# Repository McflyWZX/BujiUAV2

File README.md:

# BujiCore(AllwinnerH5CoreBoard)
 基于全志H5的M.2接口核心板，搭载4*DDR3、eMMC。
 板子使用KiCAD设计
 designed with KiCAD

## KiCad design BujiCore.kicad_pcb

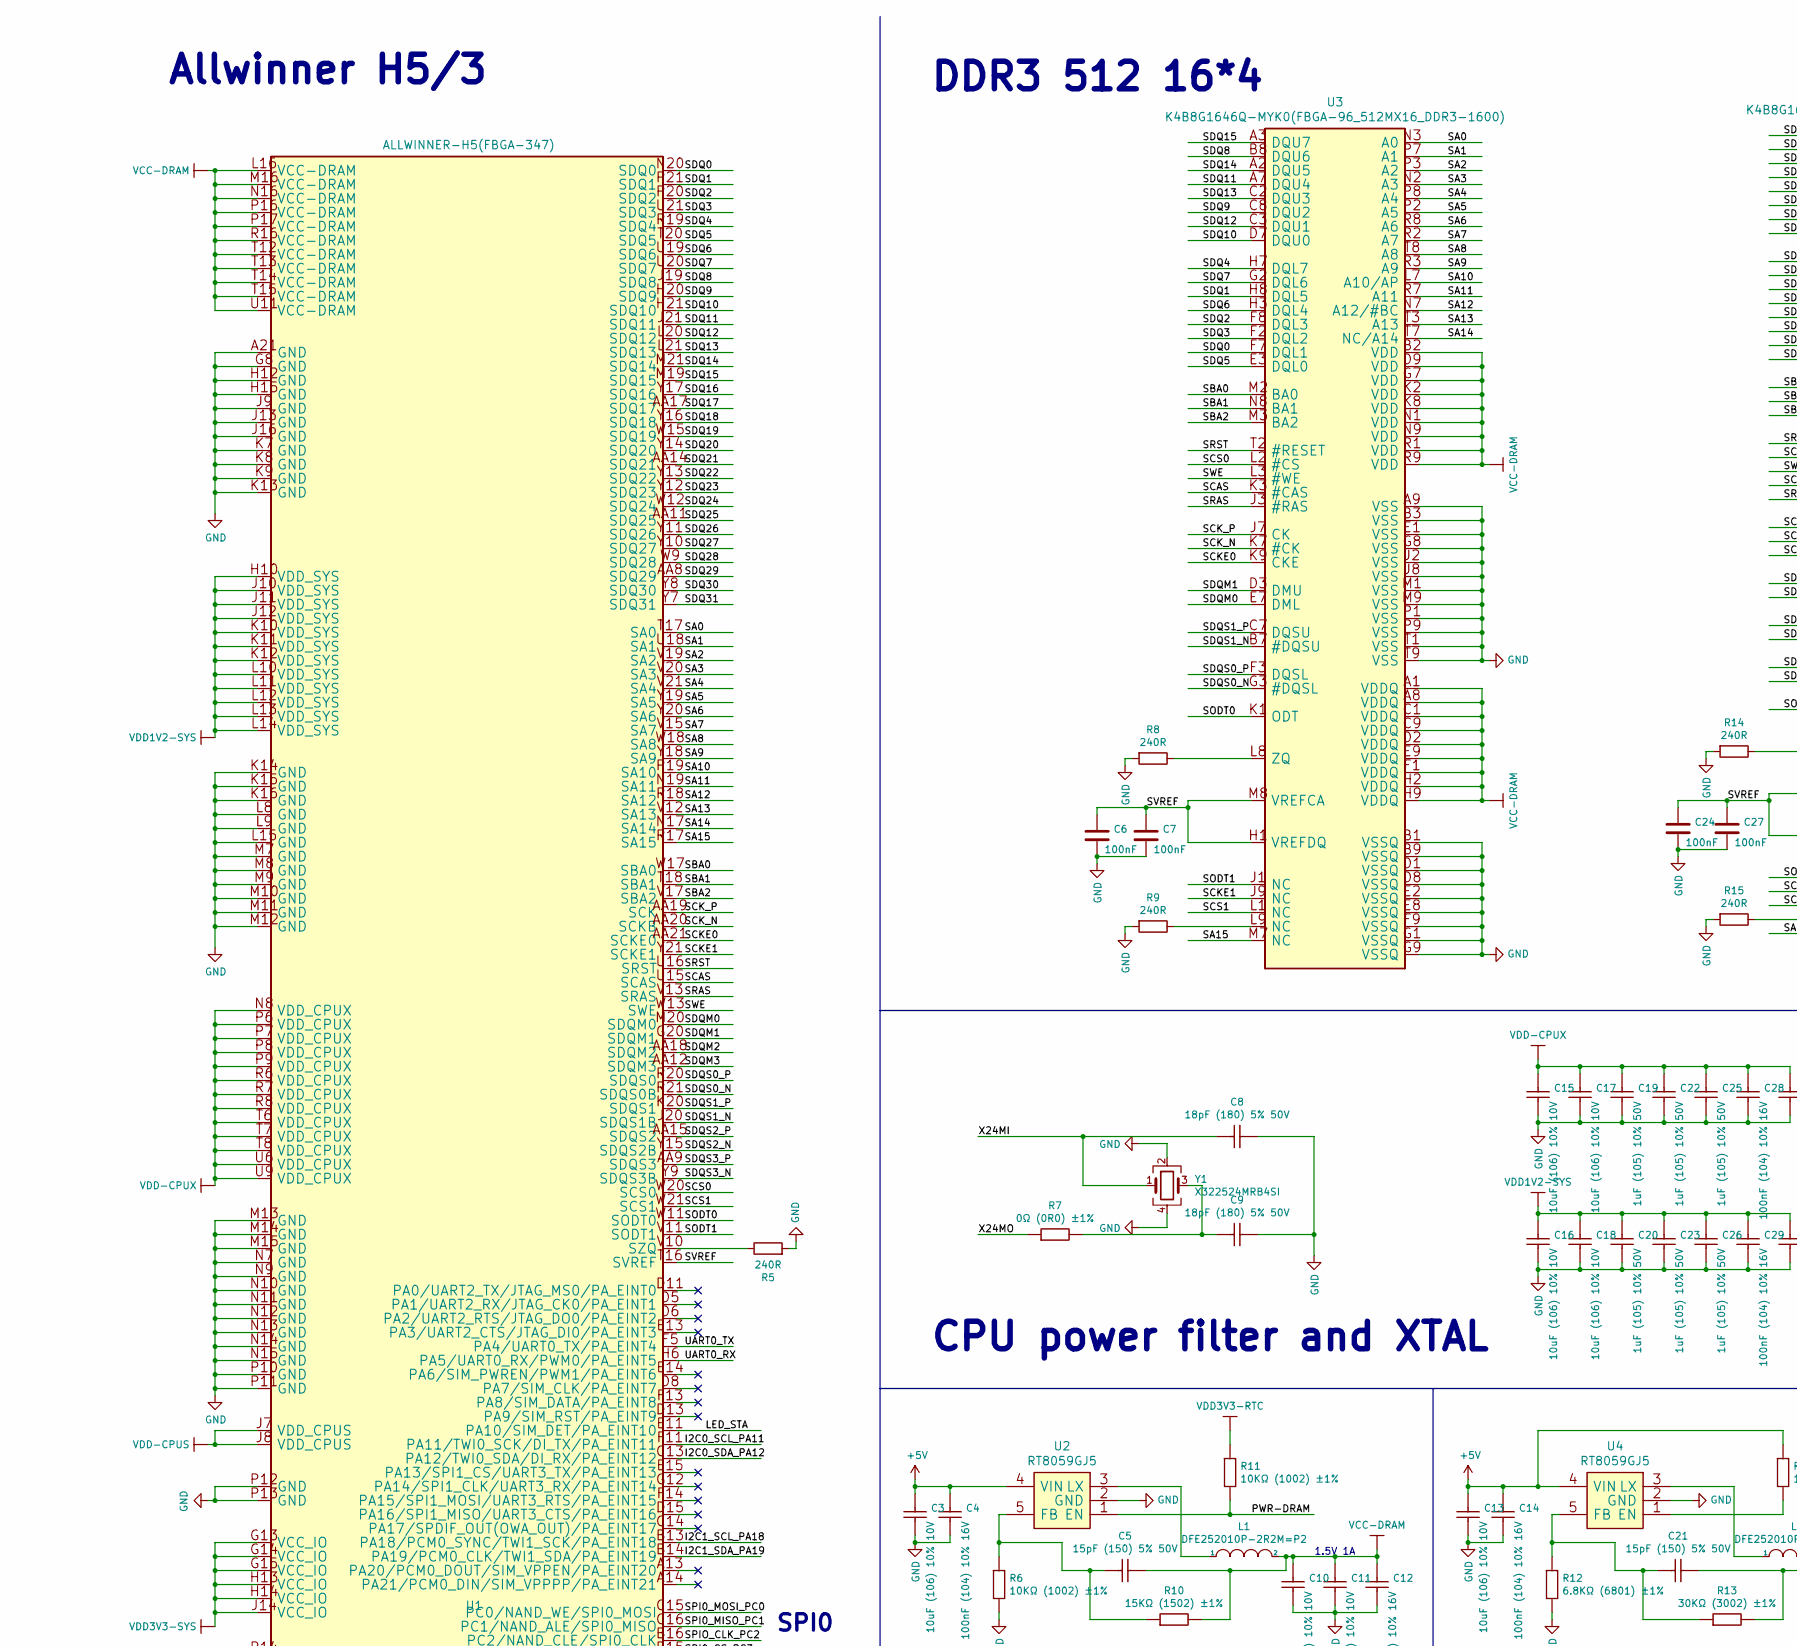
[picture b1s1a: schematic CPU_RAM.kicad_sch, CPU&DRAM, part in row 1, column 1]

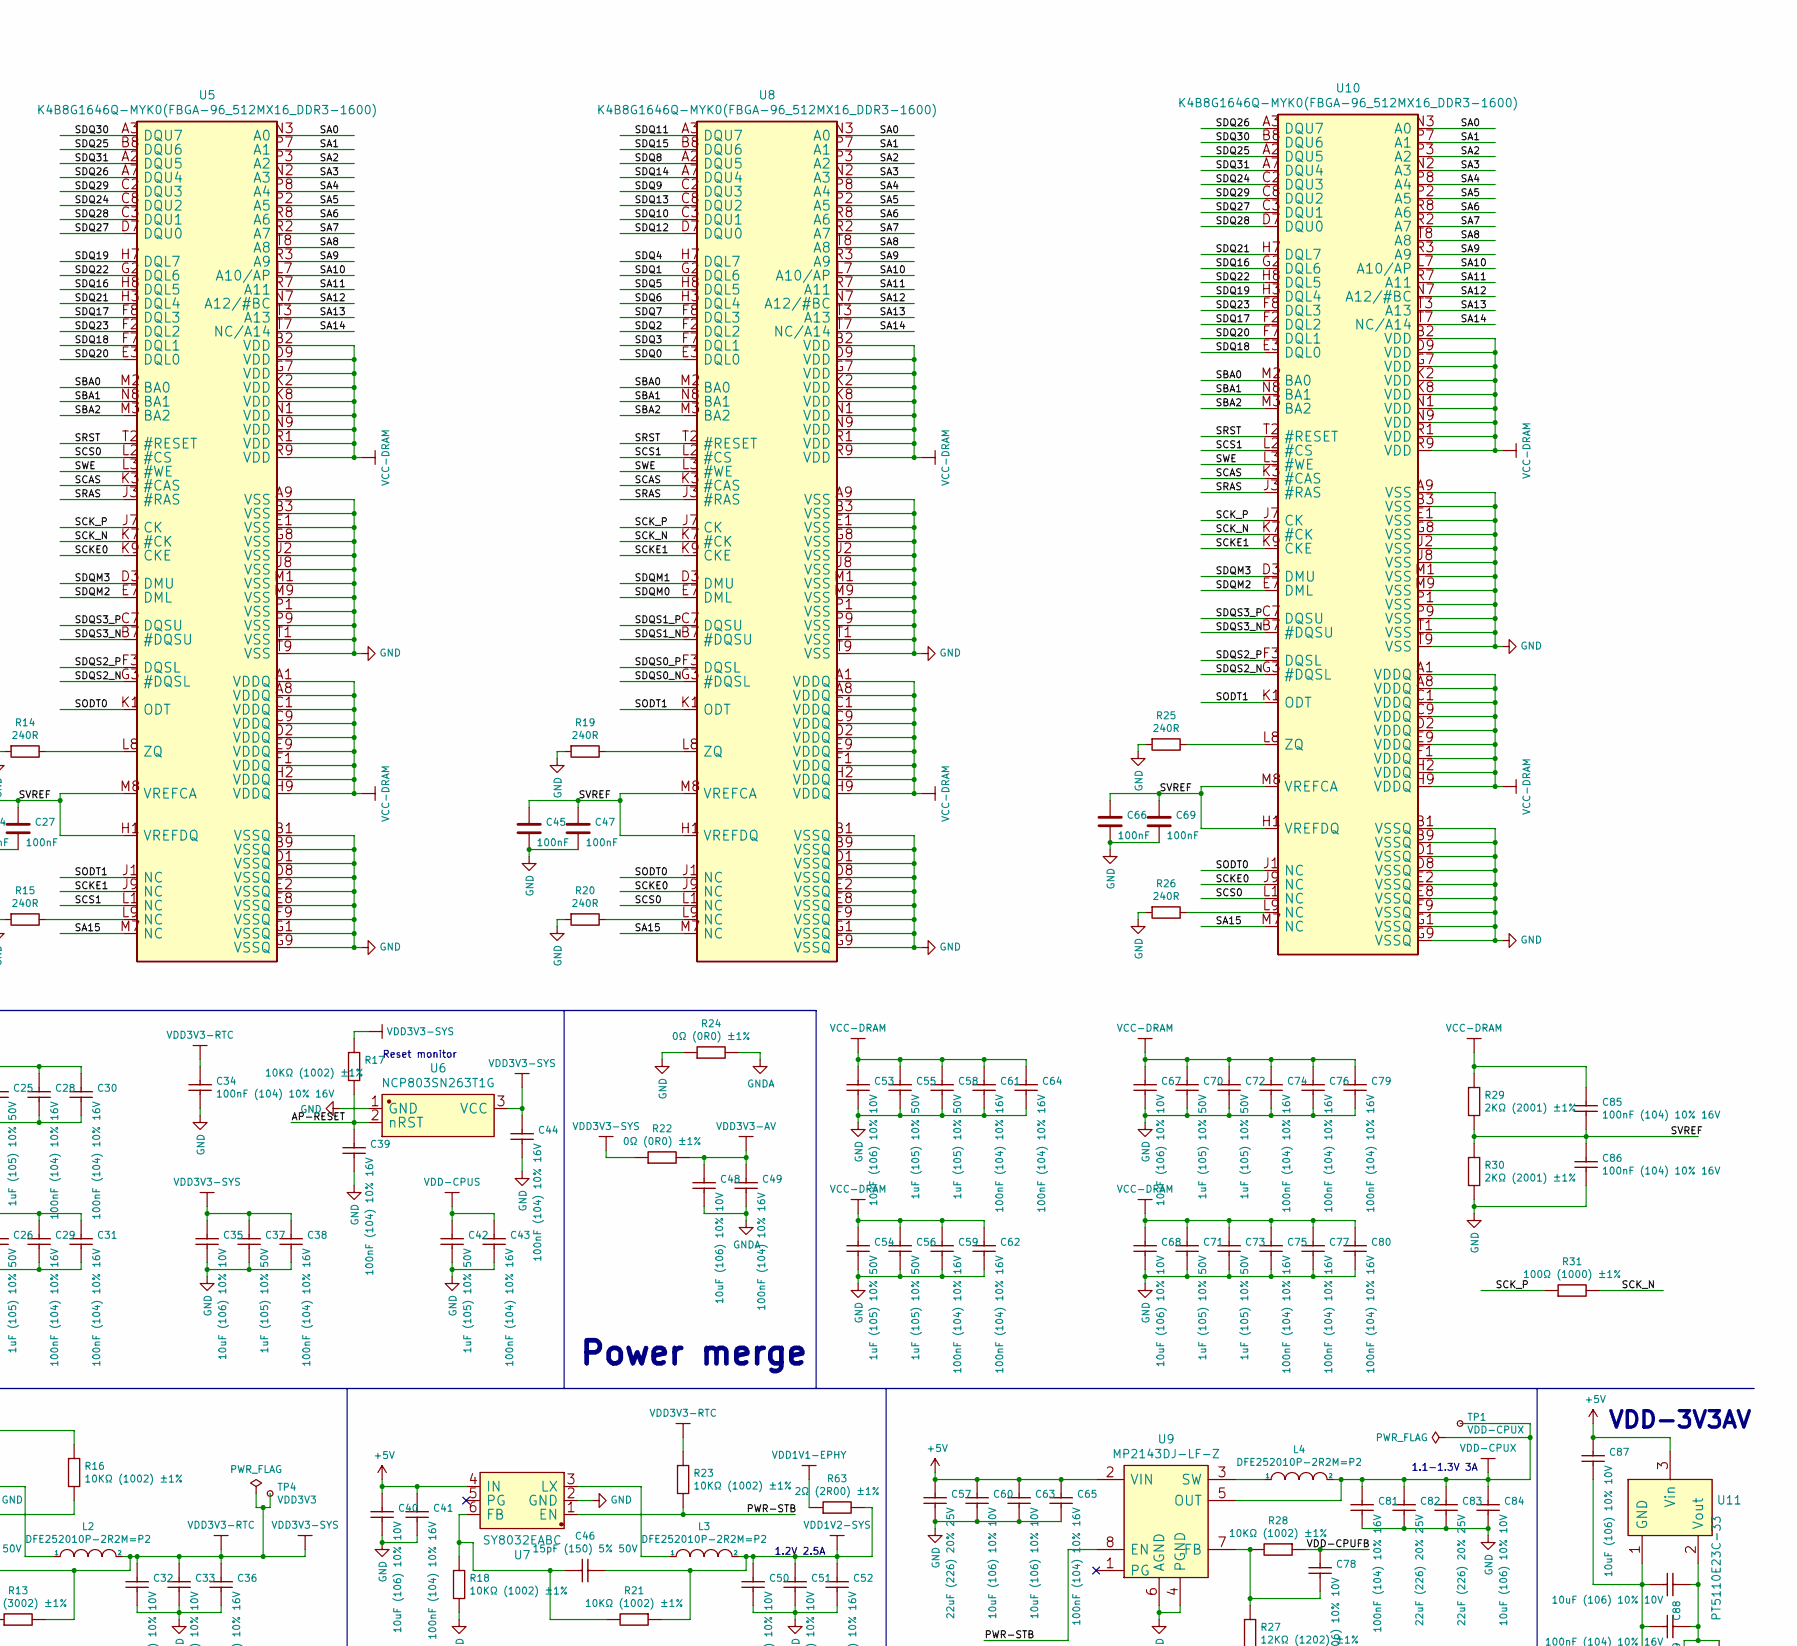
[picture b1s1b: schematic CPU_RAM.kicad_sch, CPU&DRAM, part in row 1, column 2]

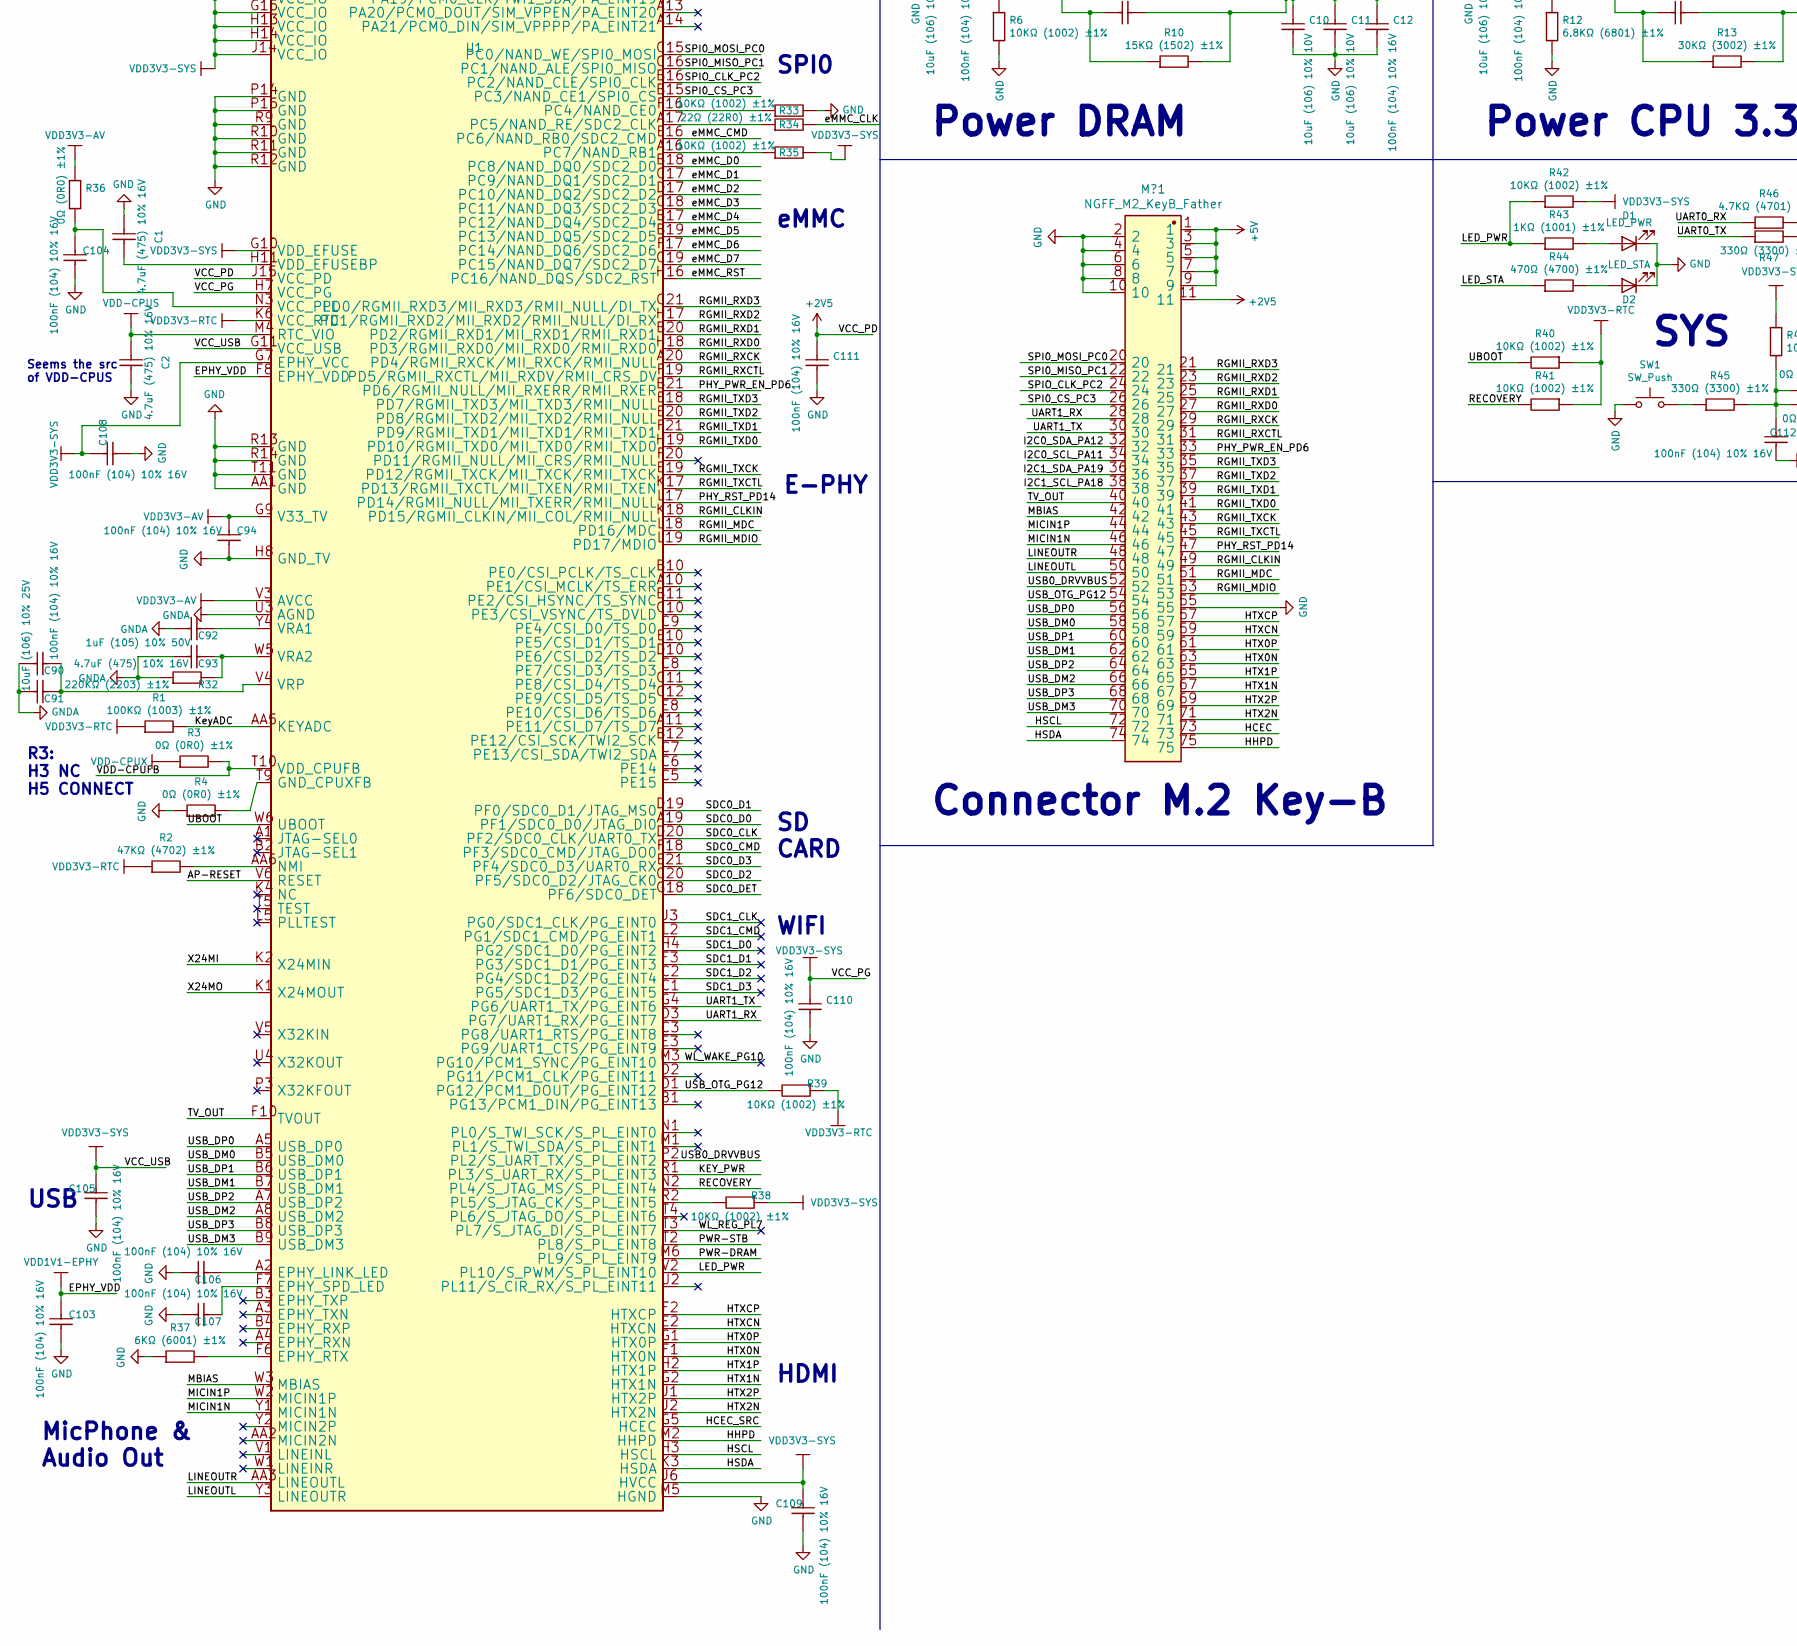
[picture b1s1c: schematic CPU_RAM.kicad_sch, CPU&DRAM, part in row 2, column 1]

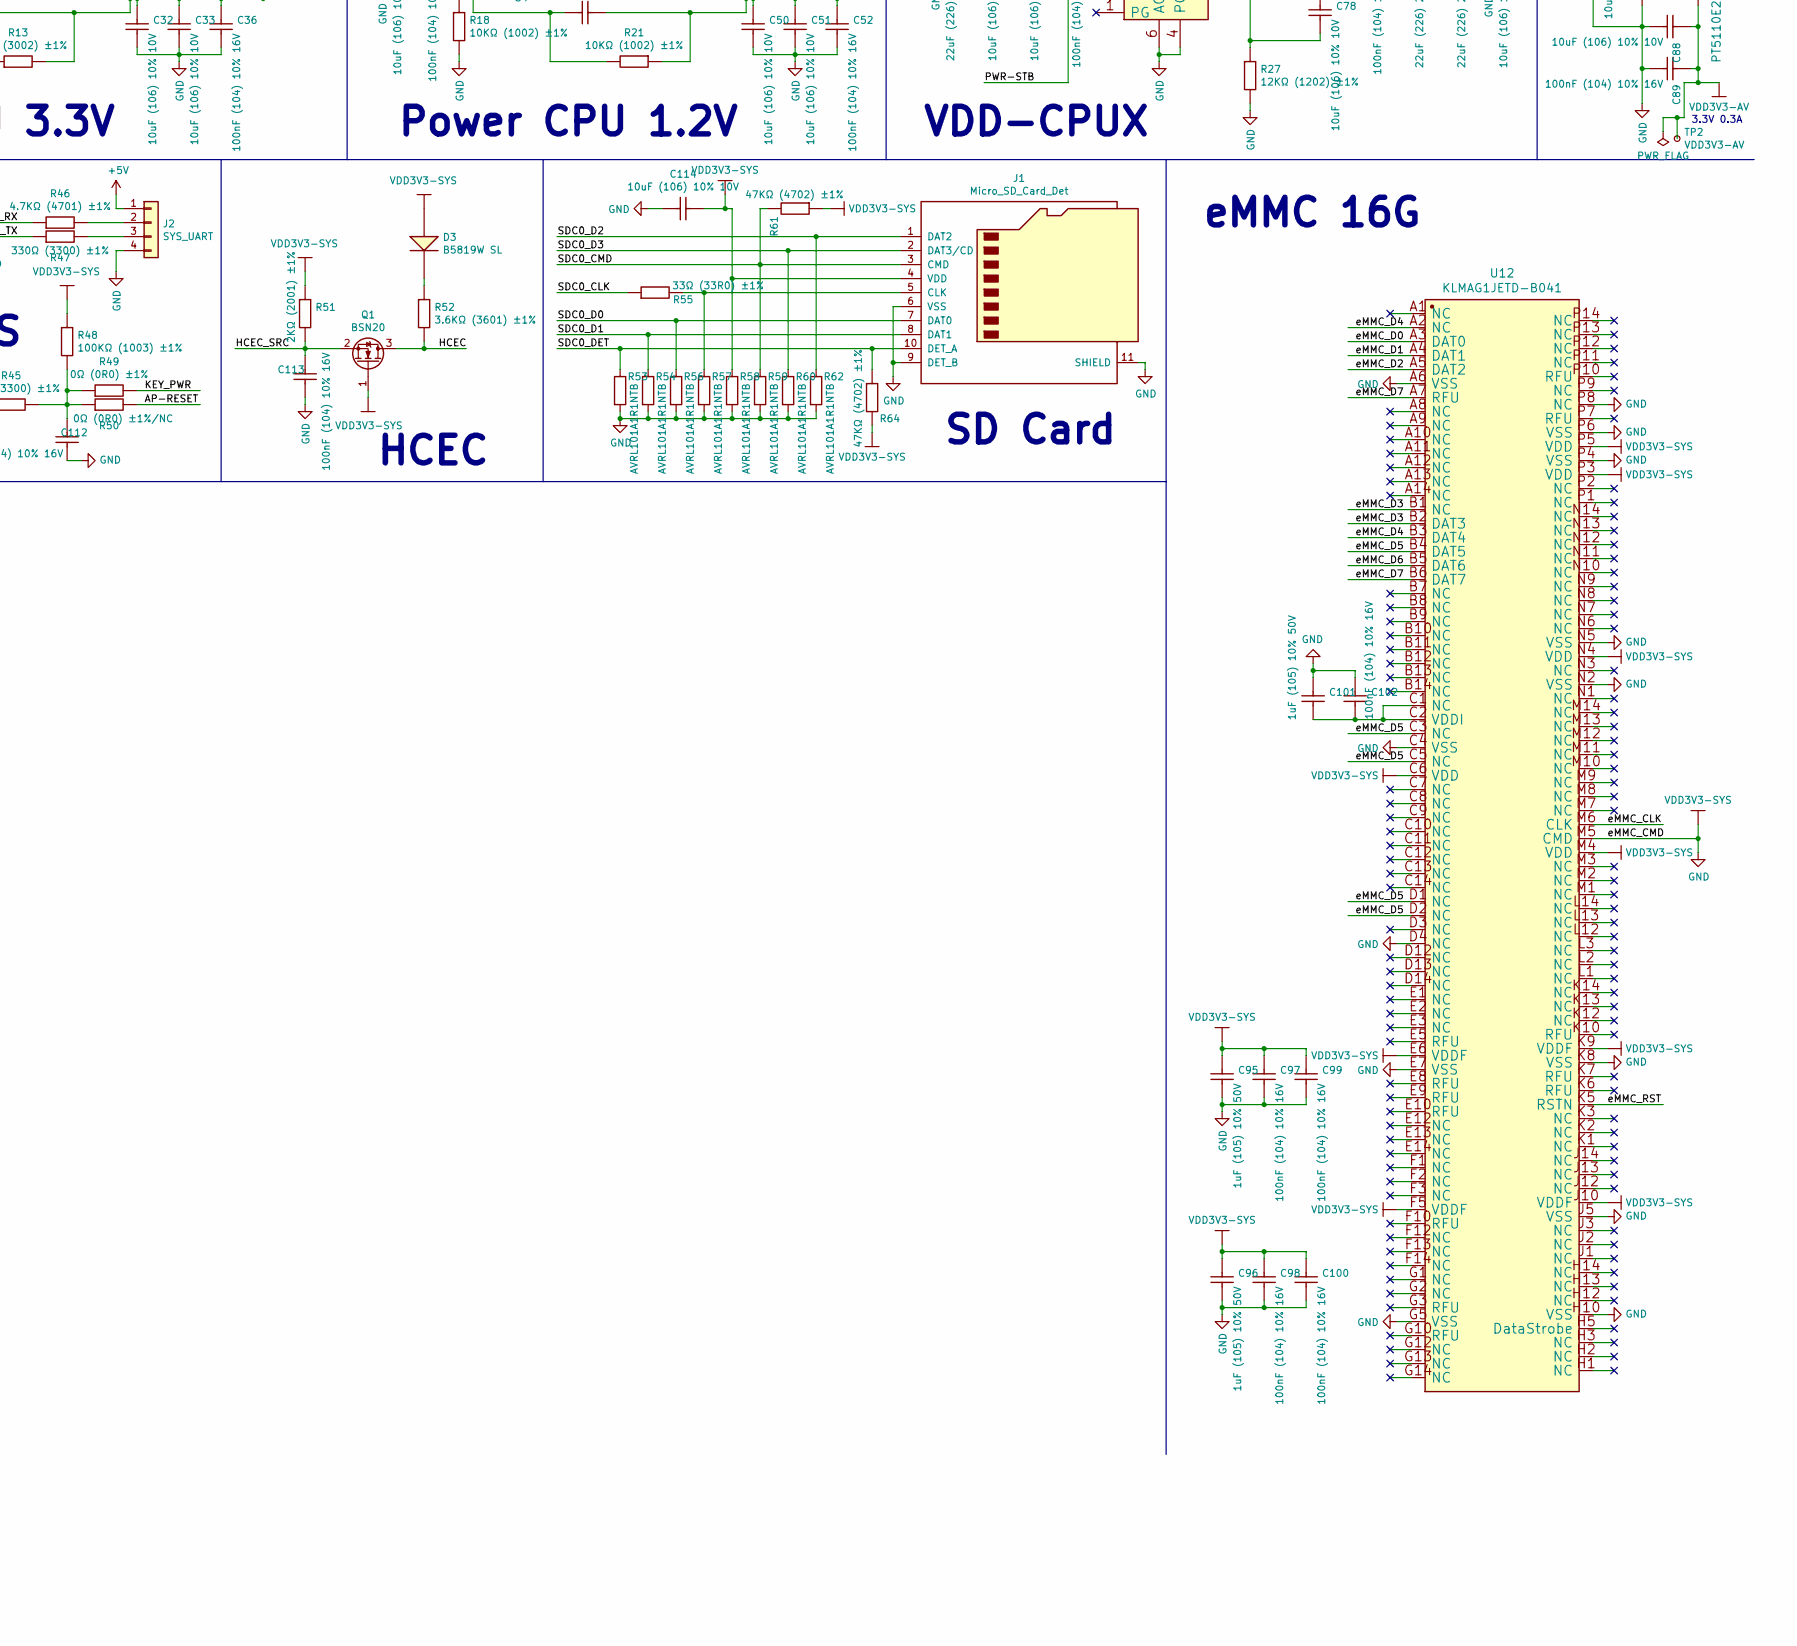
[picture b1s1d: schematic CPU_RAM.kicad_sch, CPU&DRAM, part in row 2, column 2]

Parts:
C1, C2, C93: 0603_4.7uF__475_10%_16V; 0603_C
C3, C10, C11, C13, C15, C16, C17, C18, C32, C33, C35, C40, C48, C50, C51, C53, C60, C63, C67, C68, C78, C84, C87, C88, C114: 0603_10uF__106_10%_10V; 0603_C
C4, C12, C14, C28, C29, C30, C31, C34, C36, C38, C39, C41, C43, C44, C49, C52, C59, C61, C62, C64, C65, C74, C75, C76, C77, C79, C80, C81, C85, C86, C89, C90, C94, C97, C98, C99, C100, C102, C103, C104, C105, C106, C107, C108, C109, C110, C111, C112, C113: 0402_100nF__104_10%_16V; 0402_C
C5, C21, C46: 0402_15pF__150_5%_50V; 0402_C
C6, C7, C24, C27, C45, C47, C66, C69: 100nF; 0402_C
C8, C9: 0402_18pF__180_5%_50V; 0402_C
C19, C20, C22, C23, C25, C26, C37, C42, C54, C55, C56, C58, C70, C71, C72, C73, C95, C96: 1uF_0402_105_10%_50V; 0603_C
C57, C82, C83: 0805_22uF__226_20%_25V; 0805_C
C91: 0805_10uF__106_10%_25V; 0805_C
C92, C101: 0603_1uF__105_10%_50V; 0603_C
D1: LED_PWR; LED_0603_1608Metric
D2: LED_STA; LED_0603_1608Metric
D3: SOD-123_B5819W__SL; SOD-123
J1: Micro_SD_Card_Det; microSD_HC_Hirose_DM3D-SF
J2: SYS_UART; PinSocket_1x04_P1.27mm_Vertical_SMD_Pin1Right
L1, L2, L3, L4: DFE252010P-2R2M=P2; L_1008_2520Metric
M?1: NGFF_M2_KeyB_Father; NGFF_B
Q1: BSN20; SOT-23
R1, R48: 0402_100KΩ__1003_1%; 0402_R
R2, R61, R64: 0402_47KΩ__4702_1%; 0402_R
R3, R4, R7, R22, R24, R36, R49, R50: 0402_0Ω__0R0_1%; 0402_R
R5, R8, R9, R14, R15, R19, R20, R25, R26: 240R; 0402_R
R6, R11, R16, R17, R18, R21, R23, R28, R33, R35, R38, R39, R40, R41, R42: 0402_10KΩ__1002_1%; 0402_R
R10: 0402_15KΩ__1502_1%; 0402_R
R12: 0402_6.8KΩ__6801_1%; 0402_R
R13: 0402_30KΩ__3002_1%; 0402_R
R27: 0402_12KΩ__1202_1%; 0402_R
R29, R30, R51: 0402_2KΩ__2001_1%; 0402_R
R31: 0402_100Ω__1000_1%; 0402_R
R32: 0402_220KΩ__2203_1%; 0402_R
R34: 0402_22Ω__22R0_1%; 0402_R
R37: 0402_6KΩ__6001_1%; 0402_R
R43: 0402_1KΩ__1001_1%; 0402_R
R44: 0402_470Ω__4700_1%; 0402_R
R45, R47: 0402_330Ω__3300_1%; 0402_R
R46: 0402_4.7KΩ__4701_1%; 0402_R
R52: 0603_3.6KΩ__3601_1%; 0603_R
R53, R54, R56, R57, R58, R59, R60, R62: AVRL101A1R1NTB; 0402_R
R55: 0402_33Ω__33R0_1%; 0402_R
R63: 0603_2Ω__2R00_1%; 0603_R
SW1: SW_Push; SW_SPST_B3U-1000P
TP1: VDD-CPUX; TestPoint_Pad_D1.5mm
TP2: VDD3V3-AV; TestPoint_Pad_D1.5mm
TP4: VDD3V3; TestPoint_Pad_D1.5mm
U1: ALLWINNER-H5(FBGA-347); BGA-347_L14.0-W14.0-R21-C21-3C
U2, U4: RT8059GJ5; SOT-23-5_L3.0-W1.7-P0.95-LS2C1
U3, U5, U8, U10: K4B8G1646Q-MYK0(FBGA-96_512MX16_DDR3-1600); FBGA-96_L13.5-W7.5-R16-C6-P096
U6: NCP803SN263T1G; SOT-23W
U7: SY8032EABC; SOT-23-6_L2.9-W1.6-P0.95-LS2E0
U9: MP2143DJ-LF-Z; TSOT-23-8_L2.9-W1.6-P0.65-LSE1
U11: PT5110E23C-33; SOT-23-3_L2.9-W1.6-P1.90-LS2D8
U12: KLMAG1JETD-B041; FBGA-153_L13.0-W11.5-P0.50_K69
Y1: X322524MRB4SI; Crystal_SMD_3225-4Pin_3.2x2.5mm

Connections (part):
1: C103.2, R63.1, U1.F8 (EPHY_VDD)
+2V5: C111.1, M?1.11, U1.J15 (VCC_PD)
+5V: C3.1, C4.1, C13.1, C14.1, C40.1, C41.1, C57.1, C60.1, C63.1, C65.1, C87.1, J2.1, M?1.1, M?1.3, M?1.5, M?1.7, M?1.9, R16.1, U2.4 (VIN), U4.4 (VIN), U7.4 (IN), U9.2 (VIN), U11.3 (Vin)
/CPU_RAM/AP-RESET: C39.1, R17.2, R50.2, U1.V6 (RESET), U6.2 (nRST)
/CPU_RAM/HCEC: M?1.73, Q1.3 (D), R52.2
/CPU_RAM/HCEC_SRC: C113.1, Q1.2 (S), R51.2, U1.G5 (HCEC)
/CPU_RAM/HHPD: M?1.75, U1.M2 (HHPD)
/CPU_RAM/HSCL: M?1.72, U1.H3 (HSCL)
/CPU_RAM/HSDA: M?1.74, U1.K3 (HSDA)
/CPU_RAM/HTX0N: M?1.63, U1.F1 (HTX0N)
/CPU_RAM/HTX0P: M?1.61, U1.G1 (HTX0P)
/CPU_RAM/HTX1N: M?1.67, U1.G2 (HTX1N)
/CPU_RAM/HTX1P: M?1.65, U1.H2 (HTX1P)
/CPU_RAM/HTX2N: M?1.71, U1.J2 (HTX2N)
/CPU_RAM/HTX2P: M?1.69, U1.J1 (HTX2P)
/CPU_RAM/HTXCN: M?1.59, U1.E2 (HTXCN)
/CPU_RAM/HTXCP: M?1.57, U1.F2 (HTXCP)
/CPU_RAM/I2C0_SCL_PA11: M?1.34, U1.F11 (PA11/TWI0_SCK/DI_TX/PA_EINT11)
/CPU_RAM/I2C0_SDA_PA12: M?1.32, U1.C13 (PA12/TWI0_SDA/DI_RX/PA_EINT12)
/CPU_RAM/I2C1_SCL_PA18: M?1.38, U1.B13 (PA18/PCM0_SYNC/TWI1_SCK/PA_EINT18)
/CPU_RAM/I2C1_SDA_PA19: M?1.36, U1.B14 (PA19/PCM0_CLK/TWI1_SDA/PA_EINT19)
/CPU_RAM/KEY_PWR: R49.2, U1.R1 (PL3/S_UART_RX/S_PL_EINT3)
/CPU_RAM/KeyADC: R1.2, U1.AA5 (KEYADC)
/CPU_RAM/LED_PWR: R42.1, R43.1, U1.V2 (PL10/S_PWM/S_PL_EINT10)
/CPU_RAM/LED_STA: R44.1, U1.E11 (PA10/SIM_DET/PA_EINT10)
/CPU_RAM/LINEOUTL: M?1.50, U1.Y3 (LINEOUTR)
/CPU_RAM/LINEOUTR: M?1.48, U1.AA3 (LINEOUTL)
/CPU_RAM/MBIAS: M?1.42, U1.W3 (MBIAS)
/CPU_RAM/MICIN1N: M?1.46, U1.Y1 (MICIN1N)
/CPU_RAM/MICIN1P: M?1.44, U1.W2 (MICIN1P)
/CPU_RAM/PHY_PWR_EN_PD6: M?1.33, U1.B21 (PD6/RGMII_NULL/MII_RXERR/RMII_RXER)
/CPU_RAM/PHY_RST_PD14: M?1.47, U1.L17 (PD14/RGMII_NULL/MII_TXERR/RMII_NULL)
/CPU_RAM/PWR-DRAM: R11.2, U1.M6 (PL9/S_PL_EINT9), U2.1 (EN)
/CPU_RAM/PWR-STB: R23.2, U1.T2 (PL8/S_PL_EINT8), U7.1 (EN), U9.8 (EN)
/CPU_RAM/RECOVERY: R41.2, U1.N2 (PL4/S_JTAG_MS/S_PL_EINT4)
/CPU_RAM/RGMII_CLKIN: M?1.49, U1.K18 (PD15/RGMII_CLKIN/MII_COL/RMII_NULL)
/CPU_RAM/RGMII_MDC: M?1.51, U1.L18 (PD16/MDC)
/CPU_RAM/RGMII_MDIO: M?1.53, U1.L19 (PD17/MDIO)
/CPU_RAM/RGMII_RXCK: M?1.29, U1.A20 (PD4/RGMII_RXCK/MII_RXCK/RMII_NULL)
/CPU_RAM/RGMII_RXCTL: M?1.31, U1.F19 (PD5/RGMII_RXCTL/MII_RXDV/RMII_CRS_DV)
/CPU_RAM/RGMII_RXD0: M?1.27, U1.H18 (PD3/RGMII_RXD0/MII_RXD0/RMII_RXD0)
/CPU_RAM/RGMII_RXD1: M?1.25, U1.B20 (PD2/RGMII_RXD1/MII_RXD1/RMII_RXD1)
/CPU_RAM/RGMII_RXD2: M?1.23, U1.H17 (PD1/RGMII_RXD2/MII_RXD2/RMII_NULL/DI_RX)
/CPU_RAM/RGMII_RXD3: M?1.21, U1.C21 (PD0/RGMII_RXD3/MII_RXD3/RMII_NULL/DI_TX)
/CPU_RAM/RGMII_TXCK: M?1.43, U1.E19 (PD12/RGMII_TXCK/MII_TXCK/RMII_TXCK)
/CPU_RAM/RGMII_TXCTL: M?1.45, U1.K17 (PD13/RGMII_TXCTL/MII_TXEN/RMII_TXEN)
/CPU_RAM/RGMII_TXD0: M?1.41, U1.H19 (PD10/RGMII_TXD0/MII_TXD0/RMII_TXD0)
/CPU_RAM/RGMII_TXD1: M?1.39, U1.F21 (PD9/RGMII_TXD1/MII_TXD1/RMII_TXD1)
/CPU_RAM/RGMII_TXD2: M?1.37, U1.E20 (PD8/RGMII_TXD2/MII_TXD2/RMII_NULL)
/CPU_RAM/RGMII_TXD3: M?1.35, U1.E18 (PD7/RGMII_TXD3/MII_TXD3/RMII_NULL)
/CPU_RAM/SA0: U1.T17 (SA0), U3.N3 (A0), U5.N3 (A0), U8.N3 (A0), U10.N3 (A0)
/CPU_RAM/SA1: U1.U18 (SA1), U3.P7 (A1), U5.P7 (A1), U8.P7 (A1), U10.P7 (A1)
/CPU_RAM/SA2: U1.V19 (SA2), U3.P3 (A2), U5.P3 (A2), U8.P3 (A2), U10.P3 (A2)
/CPU_RAM/SA3: U1.V20 (SA3), U3.N2 (A3), U5.N2 (A3), U8.N2 (A3), U10.N2 (A3)
/CPU_RAM/SA4: U1.V21 (SA4), U3.P8 (A4), U5.P8 (A4), U8.P8 (A4), U10.P8 (A4)
/CPU_RAM/SA5: U1.Y19 (SA5), U3.P2 (A5), U5.P2 (A5), U8.P2 (A5), U10.P2 (A5)
/CPU_RAM/SA6: U1.Y20 (SA6), U3.R8 (A6), U5.R8 (A6), U8.R8 (A6), U10.R8 (A6)
/CPU_RAM/SA7: U1.V15 (SA7), U3.R2 (A7), U5.R2 (A7), U8.R2 (A7), U10.R2 (A7)
/CPU_RAM/SA8: U1.W18 (SA8), U3.T8 (A8), U5.T8 (A8), U8.T8 (A8), U10.T8 (A8)
/CPU_RAM/SA9: U1.Y18 (SA9), U3.R3 (A9), U5.R3 (A9), U8.R3 (A9), U10.R3 (A9)
/CPU_RAM/SA10: U1.P19 (SA10), U3.L7 (A10/AP), U5.L7 (A10/AP), U8.L7 (A10/AP), U10.L7 (A10/AP)
/CPU_RAM/SA11: U1.N19 (SA11), U3.R7 (A11), U5.R7 (A11), U8.R7 (A11), U10.R7 (A11)
/CPU_RAM/SA12: U1.R18 (SA12), U3.N7 (A12/#BC), U5.N7 (A12/#BC), U8.N7 (A12/#BC), U10.N7 (A12/#BC)
/CPU_RAM/SA13: U1.V12 (SA13), U3.T3 (A13), U5.T3 (A13), U8.T3 (A13), U10.T3 (A13)
/CPU_RAM/SA14: U1.N17 (SA14), U3.T7 (NC/A14), U5.T7 (NC/A14), U8.T7 (NC/A14), U10.T7 (NC/A14)
/CPU_RAM/SA15: U1.R17 (SA15), U3.M7 (NC), U5.M7 (NC), U8.M7 (NC), U10.M7 (NC)
/CPU_RAM/SBA0: U1.W17 (SBA0), U3.M2 (BA0), U5.M2 (BA0), U8.M2 (BA0), U10.M2 (BA0)
/CPU_RAM/SBA1: U1.T18 (SBA1), U3.N8 (BA1), U5.N8 (BA1), U8.N8 (BA1), U10.N8 (BA1)
/CPU_RAM/SBA2: U1.V17 (SBA2), U3.M3 (BA2), U5.M3 (BA2), U8.M3 (BA2), U10.M3 (BA2)
/CPU_RAM/SCAS: U1.U15 (SCAS), U3.K3 (#CAS), U5.K3 (#CAS), U8.K3 (#CAS), U10.K3 (#CAS)
/CPU_RAM/SCKE0: U1.AA21 (SCKE0), U3.K9 (CKE), U5.K9 (CKE), U8.J9 (NC), U10.J9 (NC)
/CPU_RAM/SCKE1: U1.Y21 (SCKE1), U3.J9 (NC), U5.J9 (NC), U8.K9 (CKE), U10.K9 (CKE)
/CPU_RAM/SCK_N: R31.2, U1.AA20 (SCKB), U3.K7 (#CK), U5.K7 (#CK), U8.K7 (#CK), U10.K7 (#CK)
/CPU_RAM/SCK_P: R31.1, U1.AA19 (SCK), U3.J7 (CK), U5.J7 (CK), U8.J7 (CK), U10.J7 (CK)
/CPU_RAM/SCS0: U1.W20 (SCS0), U3.L2 (#CS), U5.L2 (#CS), U8.L1 (NC), U10.L1 (NC)
/CPU_RAM/SCS1: U1.W21 (SCS1), U3.L1 (NC), U5.L1 (NC), U8.L2 (#CS), U10.L2 (#CS)
/CPU_RAM/SDC0_CLK: R55.1, U1.D20 (PF2/SDC0_CLK/UART0_TX)
/CPU_RAM/SDC0_CMD: J1.3 (CMD), R59.1, R61.2, U1.F18 (PF3/SDC0_CMD/JTAG_DO0)
/CPU_RAM/SDC0_D0: J1.7 (DAT0), R56.1, U1.A19 (PF1/SDC0_D0/JTAG_DI0)
/CPU_RAM/SDC0_D1: J1.8 (DAT1), R54.1, U1.D19 (PF0/SDC0_D1/JTAG_MS0)
/CPU_RAM/SDC0_D2: J1.1 (DAT2), R62.1, U1.C20 (PF5/SDC0_D2/JTAG_CK0)
/CPU_RAM/SDC0_D3: J1.2 (DAT3/CD), R60.1, U1.E21 (PF4/SDC0_D3/UART0_RX)
/CPU_RAM/SDC0_DET: J1.10 (DET_A), R53.1, R64.1, U1.G18 (PF6/SDC0_DET)
/CPU_RAM/SDC1_CLK: U1.J3 (PG0/SDC1_CLK/PG_EINT0)
/CPU_RAM/SDC1_CMD: U1.L2 (PG1/SDC1_CMD/PG_EINT1)
/CPU_RAM/SDC1_D0: U1.H4 (PG2/SDC1_D0/PG_EINT2)
/CPU_RAM/SDC1_D1: U1.F3 (PG3/SDC1_D1/PG_EINT3)
/CPU_RAM/SDC1_D2: U1.C2 (PG4/SDC1_D2/PG_EINT4)
/CPU_RAM/SDC1_D3: U1.C1 (PG5/SDC1_D3/PG_EINT5)
/CPU_RAM/SDQ0: U1.N20 (SDQ0), U3.F7 (DQL1), U8.E3 (DQL0)
/CPU_RAM/SDQ1: U1.P21 (SDQ1), U3.H8 (DQL5), U8.G2 (DQL6)
/CPU_RAM/SDQ2: U1.P20 (SDQ2), U3.F8 (DQL3), U8.F2 (DQL2)
/CPU_RAM/SDQ3: U1.U21 (SDQ3), U3.F2 (DQL2), U8.F7 (DQL1)
/CPU_RAM/SDQ4: U1.R19 (SDQ4), U3.H7 (DQL7), U8.H7 (DQL7)
/CPU_RAM/SDQ5: U1.T20 (SDQ5), U3.E3 (DQL0), U8.H8 (DQL5)
/CPU_RAM/SDQ6: U1.U19 (SDQ6), U3.H3 (DQL4), U8.H3 (DQL4)
/CPU_RAM/SDQ7: U1.U20 (SDQ7), U3.G2 (DQL6), U8.F8 (DQL3)
/CPU_RAM/SDQ8: U1.J19 (SDQ8), U3.B8 (DQU6), U8.A2 (DQU5)
/CPU_RAM/SDQ9: U1.H20 (SDQ9), U3.C8 (DQU2), U8.C2 (DQU3)
/CPU_RAM/SDQ10: U1.H21 (SDQ10), U3.D7 (DQU0), U8.C3 (DQU1)
/CPU_RAM/SDQ11: U1.J21 (SDQ11), U3.A7 (DQU4), U8.A3 (DQU7)
/CPU_RAM/SDQ12: U1.L20 (SDQ12), U3.C3 (DQU1), U8.D7 (DQU0)
/CPU_RAM/SDQ13: U1.L21 (SDQ13), U3.C2 (DQU3), U8.C8 (DQU2)
/CPU_RAM/SDQ14: U1.M21 (SDQ14), U3.A2 (DQU5), U8.A7 (DQU4)
/CPU_RAM/SDQ15: U1.M19 (SDQ15), U3.A3 (DQU7), U8.B8 (DQU6)
/CPU_RAM/SDQ16: U1.Y17 (SDQ16), U5.H8 (DQL5), U10.G2 (DQL6)
/CPU_RAM/SDQ17: U1.AA17 (SDQ17), U5.F8 (DQL3), U10.F2 (DQL2)
/CPU_RAM/SDQ18: U1.Y16 (SDQ18), U5.F7 (DQL1), U10.E3 (DQL0)
/CPU_RAM/SDQ19: U1.W15 (SDQ19), U5.H7 (DQL7), U10.H3 (DQL4)
/CPU_RAM/SDQ20: U1.Y14 (SDQ20), U5.E3 (DQL0), U10.F7 (DQL1)
/CPU_RAM/SDQ21: U1.AA14 (SDQ21), U5.H3 (DQL4), U10.H7 (DQL7)
/CPU_RAM/SDQ22: U1.Y13 (SDQ22), U5.G2 (DQL6), U10.H8 (DQL5)
/CPU_RAM/SDQ23: U1.Y12 (SDQ23), U5.F2 (DQL2), U10.F8 (DQL3)
/CPU_RAM/SDQ24: U1.W12 (SDQ24), U5.C8 (DQU2), U10.C2 (DQU3)
/CPU_RAM/SDQ25: U1.AA11 (SDQ25), U5.B8 (DQU6), U10.A2 (DQU5)
/CPU_RAM/SDQ26: U1.Y11 (SDQ26), U5.A7 (DQU4), U10.A3 (DQU7)
/CPU_RAM/SDQ27: U1.Y10 (SDQ27), U5.D7 (DQU0), U10.C3 (DQU1)
/CPU_RAM/SDQ28: U1.W9 (SDQ28), U5.C3 (DQU1), U10.D7 (DQU0)
/CPU_RAM/SDQ29: U1.AA8 (SDQ29), U5.C2 (DQU3), U10.C8 (DQU2)
/CPU_RAM/SDQ30: U1.Y8 (SDQ30), U5.A3 (DQU7), U10.B8 (DQU6)
/CPU_RAM/SDQ31: U1.Y7 (SDQ31), U5.A2 (DQU5), U10.A7 (DQU4)
/CPU_RAM/SDQM0: U1.M20 (SDQM0), U3.E7 (DML), U8.E7 (DML)
/CPU_RAM/SDQM1: U1.G20 (SDQM1), U3.D3 (DMU), U8.D3 (DMU)
/CPU_RAM/SDQM2: U1.AA18 (SDQM2), U5.E7 (DML), U10.E7 (DML)
/CPU_RAM/SDQM3: U1.AA12 (SDQM3), U5.D3 (DMU), U10.D3 (DMU)
/CPU_RAM/SDQS0_N: U1.R21 (SDQS0B), U3.G3 (#DQSL), U8.G3 (#DQSL)
/CPU_RAM/SDQS0_P: U1.R20 (SDQS0), U3.F3 (DQSL), U8.F3 (DQSL)
/CPU_RAM/SDQS1_N: U1.J20 (SDQS1B), U3.B7 (#DQSU), U8.B7 (#DQSU)
/CPU_RAM/SDQS1_P: U1.K20 (SDQS1), U3.C7 (DQSU), U8.C7 (DQSU)
/CPU_RAM/SDQS2_N: U1.Y15 (SDQS2B), U5.G3 (#DQSL), U10.G3 (#DQSL)
/CPU_RAM/SDQS2_P: U1.AA15 (SDQS2), U5.F3 (DQSL), U10.F3 (DQSL)
/CPU_RAM/SDQS3_N: U1.Y9 (SDQS3B), U5.B7 (#DQSU), U10.B7 (#DQSU)
/CPU_RAM/SDQS3_P: U1.AA9 (SDQS3), U5.C7 (DQSU), U10.C7 (DQSU)
/CPU_RAM/SODT0: U1.W11 (SODT0), U3.K1 (ODT), U5.K1 (ODT), U8.J1 (NC), U10.J1 (NC)
/CPU_RAM/SODT1: U1.V11 (SODT1), U3.J1 (NC), U5.J1 (NC), U8.K1 (ODT), U10.K1 (ODT)
/CPU_RAM/SPI0_CS_PC3: M?1.26, U1.B15 (PC3/NAND_CE1/SPI0_CS)
/CPU_RAM/SPI0_MISO_PC1: M?1.22, U1.C16 (PC1/NAND_ALE/SPI0_MISO)
/CPU_RAM/SPI0_MOSI_PC0: M?1.20, U1.C15 (PC0/NAND_WE/SPI0_MOSI)
/CPU_RAM/SPIO_CLK_PC2: M?1.24, U1.B16 (PC2/NAND_CLE/SPI0_CLK)
/CPU_RAM/SRAS: U1.V13 (SRAS), U3.J3 (#RAS), U5.J3 (#RAS), U8.J3 (#RAS), U10.J3 (#RAS)
/CPU_RAM/SRST: U1.U16 (SRST), U3.T2 (#RESET), U5.T2 (#RESET), U8.T2 (#RESET), U10.T2 (#RESET)
/CPU_RAM/SVREF: C6.2, C7.2, C24.2, C27.2, C45.2, C47.2, C66.2, C69.2, C85.2, C86.1, R29.2, R30.1, U1.T16 (SVREF), U3.H1 (VREFDQ), U3.M8 (VREFCA), U5.H1 (VREFDQ), U5.M8 (VREFCA), U8.H1 (VREFDQ), U8.M8 (VREFCA), U10.H1 (VREFDQ), U10.M8 (VREFCA)
/CPU_RAM/SWE: U1.W13 (SWE), U3.L3 (#WE), U5.L3 (#WE), U8.L3 (#WE), U10.L3 (#WE)
/CPU_RAM/TV_OUT: M?1.40, U1.F10 (TVOUT)
/CPU_RAM/UART0_RX: R46.1, U1.H6 (PA5/UART0_RX/PWM0/PA_EINT5)
/CPU_RAM/UART0_TX: R47.1, U1.F5 (PA4/UART0_TX/PA_EINT4)
/CPU_RAM/UART1_RX: M?1.28, U1.D3 (PG7/UART1_RX/PG_EINT7)
/CPU_RAM/UART1_TX: M?1.30, U1.G4 (PG6/UART1_TX/PG_EINT6)
/CPU_RAM/UBOOT: R40.2, U1.W6 (UBOOT)
/CPU_RAM/USB0_DRVVBUS: M?1.52, U1.P2 (PL2/S_UART_TX/S_PL_EINT2)
/CPU_RAM/USB_DM0: M?1.58, U1.B5 (USB_DM0)
/CPU_RAM/USB_DM1: M?1.62, U1.B7 (USB_DM1)
/CPU_RAM/USB_DM2: M?1.66, U1.A8 (USB_DM2)
/CPU_RAM/USB_DM3: M?1.70, U1.B9 (USB_DM3)
/CPU_RAM/USB_DP0: M?1.56, U1.A5 (USB_DP0)
/CPU_RAM/USB_DP1: M?1.60, U1.B6 (USB_DP1)
/CPU_RAM/USB_DP2: M?1.64, U1.A7 (USB_DP2)
/CPU_RAM/USB_DP3: M?1.68, U1.B8 (USB_DP3)
/CPU_RAM/USB_OTG_PG12: M?1.54, R39.2, U1.D1 (PG12/PCM1_DOUT/PG_EINT12)
/CPU_RAM/VDD-CPUFB: C78.1, R3.2, R28.1, U1.T10 (VDD_CPUFB)
/CPU_RAM/WL_REG_PL7: U1.T3 (PL7/S_JTAG_DI/S_PL_EINT7)
/CPU_RAM/WL_WAKE_PG10: U1.M3 (PG10/PCM1_SYNC/PG_EINT10)
/CPU_RAM/X24MI: C8.1, U1.K2 (X24MIN), Y1.1
/CPU_RAM/X24MO: R7.1, U1.K1 (X24MOUT)
/CPU_RAM/eMMC_CLK: R34.2, U12.M6 (CLK)
/CPU_RAM/eMMC_D0: U1.B18 (PC8/NAND_DQ0/SDC2_D0), U12.A3 (DAT0)
/CPU_RAM/eMMC_D1: U1.C17 (PC9/NAND_DQ1/SDC2_D1), U12.A4 (DAT1)
/CPU_RAM/eMMC_D2: U1.D17 (PC10/NAND_DQ2/SDC2_D2), U12.A5 (DAT2)
/CPU_RAM/eMMC_D3: U1.C18 (PC11/NAND_DQ3/SDC2_D3), U12.B1 (NC), U12.B2 (DAT3)
/CPU_RAM/eMMC_D4: U1.B17 (PC12/NAND_DQ4/SDC2_D4), U12.A2 (NC), U12.B3 (DAT4)
/CPU_RAM/eMMC_D5: U1.B19 (PC13/NAND_DQ5/SDC2_D5), U12.B4 (DAT5), U12.C3 (NC), U12.C5 (NC), U12.D1 (NC), U12.D2 (NC)
/CPU_RAM/eMMC_D6: U1.F17 (PC14/NAND_DQ6/SDC2_D6), U12.B5 (DAT6)
/CPU_RAM/eMMC_D7: U1.C19 (PC15/NAND_DQ7/SDC2_D7), U12.A7 (RFU), U12.B6 (DAT7)
/CPU_RAM/eMMC_RST: U1.H16 (PC16/NAND_DQS/SDC2_RST), U12.K5 (RSTN)
GND: C1.2, C2.1, C3.2, C4.2, C6.1, C7.1, C8.2, C9.2, C10.2, C11.2, C12.2, C13.2, C14.2, C15.2, C16.2, C17.2, C18.2, C19.2, C20.2, C21.2, C22.2, C23.2, C24.1, C25.2, C26.2, C27.1, C28.2, C29.2, C30.2, C31.2, C32.1, C32.2, C33.1, C33.2, C34.1, C34.2, C35.1, C35.2, C36.1, C36.2, C37.1, C37.2, C38.1, C38.2, C39.2, C40.2, C41.2, C42.2, C43.2, C44.1, C44.2, C45.1, C47.1, C50.2, C51.2, C52.2, C53.2, C54.2, C55.2, C56.2, C57.2, C58.2, C59.2, C60.2, C61.2, C62.2, C63.2, C64.2, C65.2, C66.1, C67.2, C68.2, C69.1, C70.2, C71.2, C72.2, C73.2, C74.2, C75.2, C76.2, C77.2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
GNDA: C48.2, C49.2, C90.1, C91.1, C92.1, C93.1, R24.2, R32.1, U1.U3 (AGND)
unnamed: C1.1, U1.H11 (VDD_EFUSEBP)
unnamed: C5.1, R6.1, R10.1, U2.5 (FB)
unnamed: C9.1, R7.2, Y1.3
unnamed: C21.1, R12.1, R13.1, U4.5 (FB)
unnamed: C46.1, R18.1, R21.2, U7.6 (FB)
unnamed: C78.2, R27.1, R28.2, U9.7 (FB)
unnamed: C90.2, C91.2, U1.V4 (VRP)
unnamed: C92.2, U1.Y4 (VRA1)
unnamed: C93.2, R32.2, U1.W5 (VRA2)
unnamed: C101.2, C102.2, U12.C1 (NC), U12.C2 (VDDI)
unnamed: C104.2, R36.2, U1.N3 (VCC_PLL)
unnamed: C106.2, U1.A2 (EPHY_LINK_LED)
unnamed: C107.2, U1.F7 (EPHY_SPD_LED)
unnamed: C112.1, R45.2, R48.2, R49.1, R50.1
unnamed: D1.2 (A), R43.2
unnamed: D2.2 (A), R44.2
unnamed: D3.2 (K), R52.1
unnamed: J1.5 (CLK), R55.2, R57.1
unnamed: J2.2, R46.2
unnamed: J2.3, R47.2
unnamed: L1.1, U2.3 (LX)
unnamed: L2.1, U4.3 (LX)
unnamed: L3.1, U7.3 (LX)
unnamed: L4.1, U9.3 (SW)
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
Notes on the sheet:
Power merge
Reset monitor
R3: H3 NC H5 CONNECT
SD Card
Power CPU 1.2V
DDR3 512 16*4
Power DRAM
Seems the src of VDD-CPUS
SD CARD
eMMC 16G
CPU power filter and XTAL
eMMC
MicPhone & Audio Out
SYS
SPI0
WIFI
1.1-1.3V 3A
Connector M.2 Key-B
USB
VDD-3V3AV
Allwinner H5/3
Power CPU 3.3V
3.3V 0.3A
HCEC
HDMI
1.5V 1A
VDD-CPUX
1.2V 2.5A
E-PHY

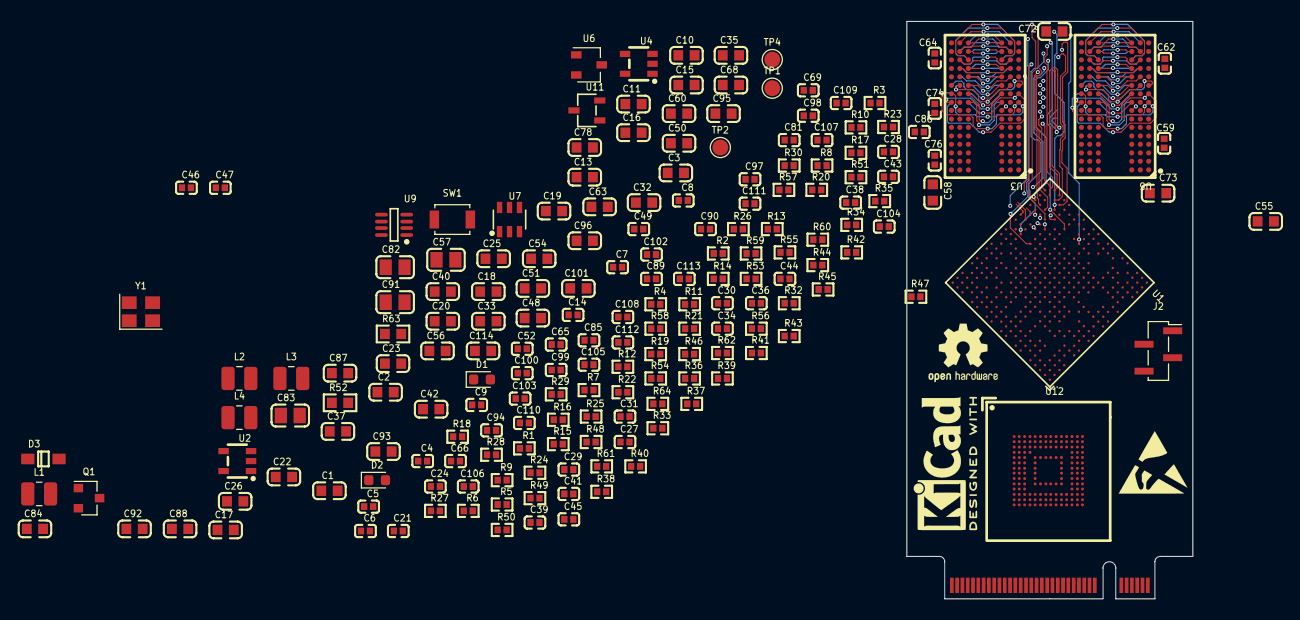
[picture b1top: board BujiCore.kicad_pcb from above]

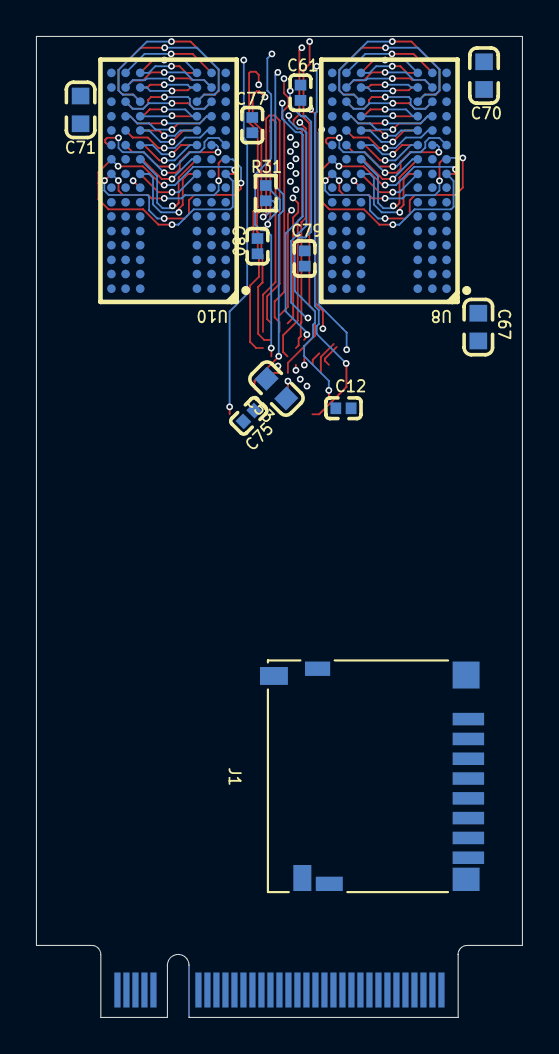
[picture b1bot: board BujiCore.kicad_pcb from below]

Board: 6 copper layers, 27.0 x 54.5 mm, 206 parts (14 on the bottom side), 215 nets.

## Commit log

2021-12-01 去除备份文件
2021-12-01 完成了许多T点到芯片的拉线工作
